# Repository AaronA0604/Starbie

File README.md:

This is a starboy-like device. I shaped it like a duck, since I plan on expanding it to be used as a debugging tool where in addition to its starboy features, it can detect if someone is speaking to it and respond in simple prompting sentences.

Controls
| Control | What it does |
|---|---|
| Button 1, first press | Opens the radial menu |
| Tilt while menu is open | Moves the selector ball; each general direction corresponds to one large sector |
| Button 1, second press | Chooses the highlighted action |
| Button 2 | Shows or hides the stats screen |
| Shake while viewing the pet | Triggers Starbie's shake reaction |

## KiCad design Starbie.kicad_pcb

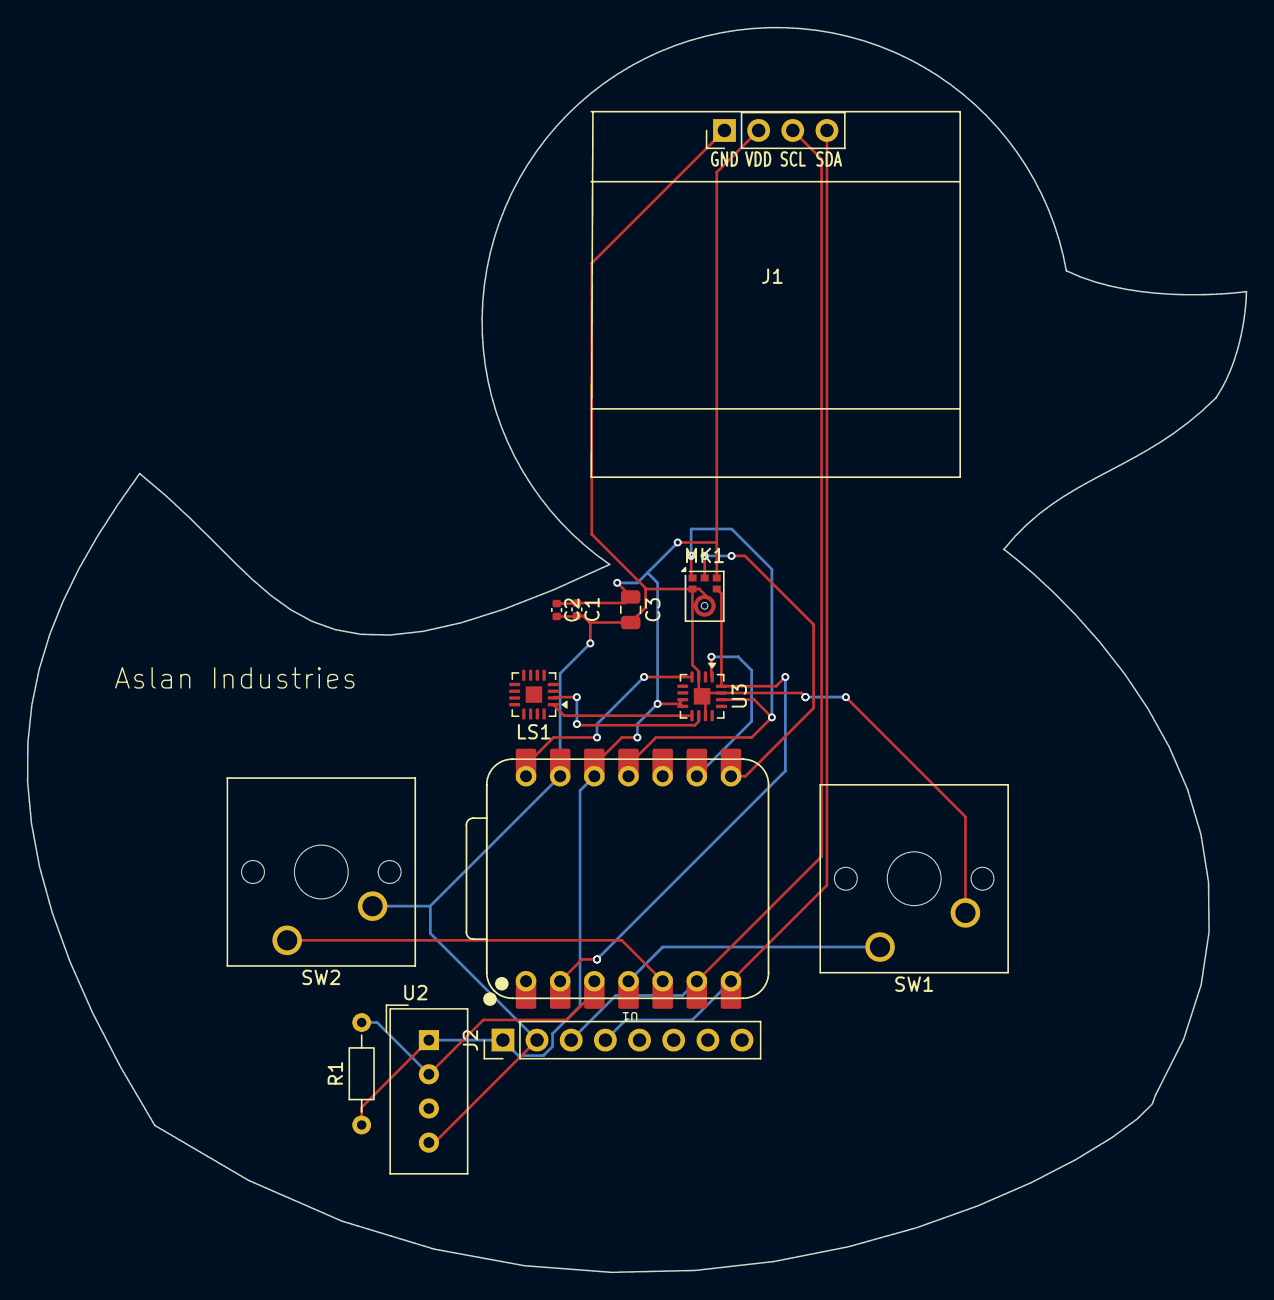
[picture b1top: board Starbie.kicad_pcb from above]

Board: 2 copper layers, 90.6 x 92.5 mm, 13 parts (0 on the bottom side), 14 nets.

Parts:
C1, C2: 0.1uF; C_0402_1005Metric
C3: 10uF; C_0805_2012Metric
J1: Conn_01x04_Pin; Display_128x64_096_I2C
J2: Conn_01x08_Pin; PinHeader_1x08_P2.54mm_Vertical
LS1: Speaker; TQFN-16-1EP_3x3mm_P0.5mm_EP1.23x1.23mm
MK1: ICS-43434; InvenSense_ICS-43434-6_3.5x2.65mm
R1: 10k; R_Axial_DIN0204_L3.6mm_D1.6mm_P7.62mm_Horizontal
SW1, SW2: SW_Push; SW_Cherry_MX_1.00u_PCB
U1: XIAO-ESP32-C3-SMD; XIAO-ESP32-C6-DIP
U2: DHT11; Aosong_DHT11_5.5x12.0_P2.54mm
U3: MAX98357A; TQFN-16-1EP_3x3mm_P0.5mm_EP1.23x1.23mm

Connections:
+3.3V: C1.1, C2.1, C3.1, J1.2, J2.1, MK1.5 (VDD), R1.1, U1.12 (3V3_OUT), U2.1 (VDD), U3.7 (VDD), U3.8 (VDD)
+5V: U1.14 (VBUS), U3.4 (~SD_MODE)
/DHT11 DATA: R1.2, U1.3 (D2), U2.2 (DATA)
/DIN: U1.9 (D8), U3.1 (DIN)
/GP102: SW1.1, U1.4 (D3)
/GP103: SW2.1, U1.5 (D4)
/SCK: MK1.4 (SCK), U1.2 (D1), U3.16 (BCLK)
/SCL: J1.3, J2.3, U1.6 (D5)
/SD: MK1.6 (SD), U1.8 (D7)
/SDA: J1.4, J2.4, U1.7 (D6)
/WS: MK1.1 (WS), U1.11 (D10), U3.14 (LRCLK)
GND: C1.2, C2.2, C3.2, J1.1, J2.2, MK1.2 (LR), MK1.3 (GND), SW1.2, SW2.2, U1.13 (GND), U2.4 (GND), U3.3 (GND), U3.11 (GND), U3.15 (GND), U3.17 (PAD)
unnamed: LS1.2, U3.10 (OUTN)
unnamed: LS1.1, U3.9 (OUTP)
